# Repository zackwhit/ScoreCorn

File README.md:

# ScoreCorn
A project to automatically score and report the points of each team playing a game of Cornhole.

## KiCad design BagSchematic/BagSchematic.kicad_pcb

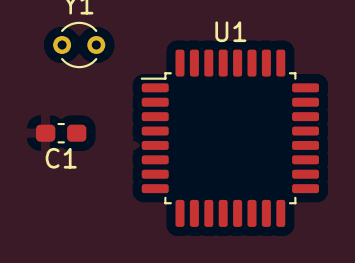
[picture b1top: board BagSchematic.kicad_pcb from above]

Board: 2 copper layers, 3 parts (0 on the bottom side), 4 nets, no tracks yet.

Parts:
C1: 1u; C_0603_1608Metric_Pad1.08x0.95mm_HandSolder
U1: STM32G071KxT; LQFP-32_7x7mm_P0.8mm
Y1: Crystal; Crystal_C26-LF_D2.1mm_L6.5mm_Vertical

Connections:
5v: C1.1, U1.4 (VDD/VDDA)
GND: C1.2, U1.5 (VSS/VSSA)
unnamed: U1.2 (OSC32_IN/PC14), Y1.2
unnamed: U1.3 (OSC32_OUT/PC15), Y1.1

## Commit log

2022-09-07 Added files
2022-09-08 Added RE DW1000 Code.drawio
2022-09-08 Added RTLS description graph
2022-09-09 Update planning diagram
2022-10-06 Worked on code and CAD models
2022-12-03 added app, made tons of changes to arudino files
2022-12-11 Made gui better, increased game code
